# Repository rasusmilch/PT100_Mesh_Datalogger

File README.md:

# PT100 + MAX31865 Temperature Data Logger (ESP32-S3, ESP-IDF)

This application turns an ESP32-S3 N8R2 into a UTC-centric PT100 data logger with FRAM-first buffering, SD-card CSV batching/verification, DS3231 RTC support, mesh streaming, and serial-console calibration.

## Hardware / wiring

All signal pins are configurable under `idf.py menuconfig -> PT100 Logger`:

- Shared SPI bus: `MOSI`, `MISO`, `SCLK`
- Chip-selects: `MAX31865 CS`, `FRAM CS`, `SD CS`
- DS3231 I2C: `SDA`, `SCL` (address selectable)

Configure mesh root/leaf role and Wi-Fi credentials in the same menu.

## Build / flash

```bash
idf.py set-target esp32s3
idf.py menuconfig   # configure pins, mesh role, batch sizes, flush thresholds
idf.py build flash monitor
```

## Logging pipeline (FRAM → SD with verification)

- Sensor task samples MAX31865 at `log interval` (NVS-backed).
- Each record is appended as a fixed-size binary struct (with CRC) to a FRAM ring buffer; the persistent header tracks read/write indices and the next sequence number.
- The SD task builds large CSV batches (~64–256 KB, configurable) from FRAM without consuming it, then:
  1. Appends the batch to the daily CSV file (`YYYY-MM-DD.csv`) with `setvbuf` buffering.
  2. `fflush()` + `fsync()`.
  3. Reads back the appended region and checks SHA-256.
  4. On mismatch: truncates to the original size and leaves FRAM untouched.
  5. On success: consumes the matching FRAM records.
- CSV header (written once per day):  
  `schema_ver,record_id,seq,epoch_utc,iso8601_local,raw_rtd_ohms,raw_temp_c,cal_temp_c,flags,node_id`
- FRAM is limited (default 32 KB); when it fills, logging pauses (no overwrite) until a flush frees space. A `fram_full` flag surfaces via `status`.

### Resume / crash safety

- On boot or day rollover the logger:
  1. Opens today’s file, truncates to the last newline if the tail was partial.
  2. Scans the tail to find the last written `seq`.
  3. Drops any FRAM records with `seq <= last_sd_seq` to guarantee no duplicates.
- If FRAM corruption is detected, consumption stops and the corrupted record can be skipped explicitly (see logs).

### Timekeeping

- DS3231 is treated as UTC and seeds system time at boot.
- Mesh root uses SNTP, updates DS3231, and broadcasts time over the mesh; leaves can request/broadcast time updates.

## Serial console commands

- `status`
- `raw` (one sample: raw/calibrated temp + resistance)
- `log interval <ms>`
- `log watermark <records>` (FRAM flush high-water mark)
- `log flush_period <ms>` (periodic SD flush interval)
- `log batch <bytes>` (target SD batch size)
- `log show`
- `cal clear`
- `cal add <raw_c> <actual_c>`
- `cal list`
- `cal apply` (1 point = offset-only; 2–4 points fit deg1–deg3)
- `flush` (best-effort FRAM→SD flush with verification)
- `diag check` (diagnostics mode only; sensor/FRAM/SD/mesh/time quick health check)

All configuration changes persist to NVS.

## Mesh / host streaming

### Mesh mode (leaf → root → broker/serial)

- Leaf nodes publish samples into the mesh; logging to FRAM continues if the
  mesh or upstream network is down.
- The root bridges mesh records to the MQTT broker and/or the DATA UART (CSV),
  and these exports are best-effort only.

### Direct Wi-Fi leaf mode (leaf → broker)

- Leaves can bypass the mesh and publish directly to the broker when configured
  for direct Wi-Fi.

FRAM/SD logging plus the DATA UART output never depend on network availability.

- Leaf nodes send samples upstream; logging to FRAM continues if mesh is down.
- Root node prints one CSV row per record over UART (after the CSV header).

Root upstream router credentials can be provided via the `wifi_ssid` /
`wifi_pass` NVS settings (from your console tooling or provisioning flow). If
those are not set, the root falls back to
`CONFIG_APP_WIFI_ROUTER_SSID` / `CONFIG_APP_WIFI_ROUTER_PASSWORD` in Kconfig.

## Test plan

1. **Calibration persistence**: Add points, apply, reboot, and confirm `status` shows the same coefficients and calibrated readings remain adjusted.
2. **Batching size**: Monitor SD writes (logic analyzer or debug prints) to confirm large buffered writes (64–256 KB) rather than per-sample writes.
3. **Crash during flush**: Pull power mid-flush; on reboot confirm the CSV tail is repaired and no duplicated `seq` appears on SD after FRAM drains.
4. **Tail repair**: Manually append a partial line to a CSV, reboot, and confirm it is truncated to the last newline automatically.
5. **Mesh resilience**: Run leaves with the root powered off; verify local FRAM accumulation and later FRAM→SD flush when root/SD returns.
6. **SD removal**: Unmount/remove SD, ensure FRAM continues to grow; remount and verify backlogged records flush with verified appends.

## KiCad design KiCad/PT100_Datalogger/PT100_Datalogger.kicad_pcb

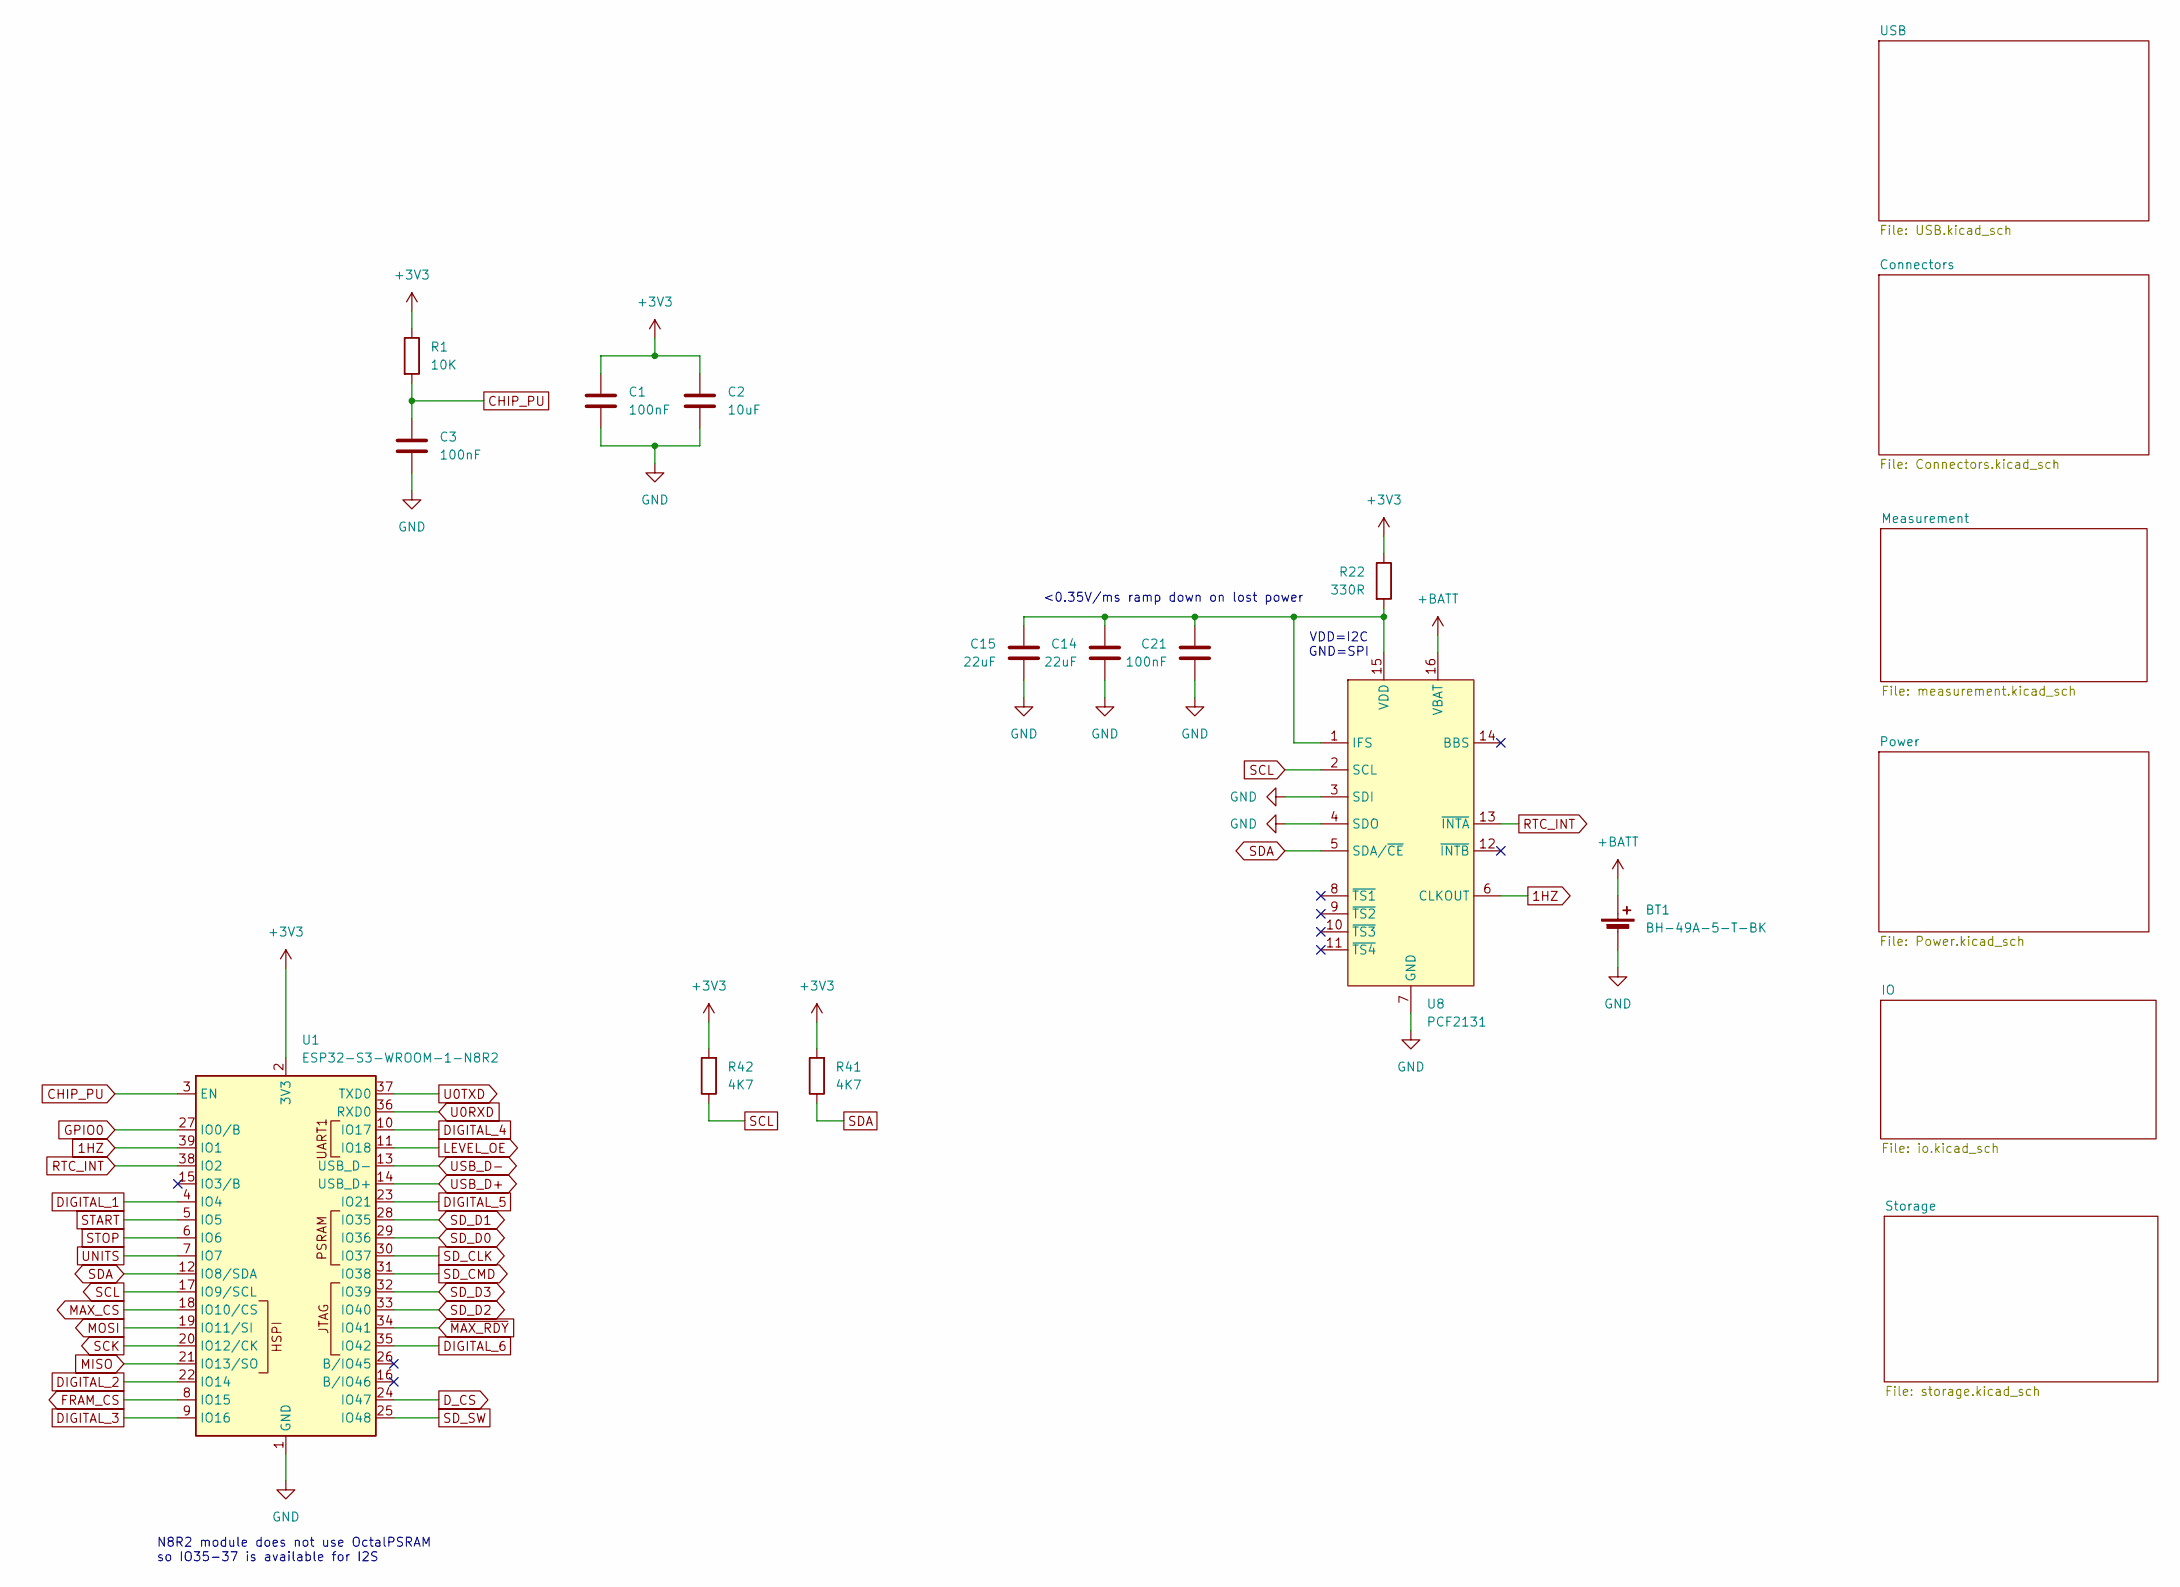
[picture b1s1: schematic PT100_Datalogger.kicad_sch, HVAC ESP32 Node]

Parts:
BT1: BH-49A-5-T-BK; BH-49A-5-T-BK_ADM
C1, C3, C21: 100nF; C_0603_1608Metric_Pad1.08x0.95mm_HandSolder
C2: 10uF; C_0805_2012Metric_Pad1.18x1.45mm_HandSolder
C14, C15: 22uF; C_0805_2012Metric_Pad1.18x1.45mm_HandSolder
R1: 10K; R_0603_1608Metric_Pad0.98x0.95mm_HandSolder
R22: 330R; R_0603_1608Metric_Pad0.98x0.95mm_HandSolder
R41, R42: 4K7; R_0603_1608Metric_Pad0.98x0.95mm_HandSolder
U1: ESP32-S3-WROOM-1-N8R2; ESP32-S3-WROOM-1
U8: PCF2131; 16-HLSON

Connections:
1HZ: U1.39 (IO1), U8.6 (CLKOUT)
+3V3: C1.1, C2.1, R1.1, R22.1, R41.2, R42.2, U1.2 (3V3); also elsewhere on the board
+BATT: BT1.1 (+), U8.16 (VBAT)
CHIP_PU: C3.1, R1.2, U1.3 (EN); also elsewhere on the board
DIGITAL_1: U1.4 (IO4); also elsewhere on the board
DIGITAL_2: U1.22 (IO14); also elsewhere on the board
DIGITAL_3: U1.9 (IO16); also elsewhere on the board
DIGITAL_4: U1.10 (IO17); also elsewhere on the board
DIGITAL_5: U1.23 (IO21); also elsewhere on the board
DIGITAL_6: U1.35 (IO42); also elsewhere on the board
D_CS: U1.24 (IO47); also elsewhere on the board
FRAM_CS: U1.8 (IO15); also elsewhere on the board
GND: BT1.2 (-), C1.2, C2.2, C3.2, C14.2, C15.2, C21.2, U1.1 (GND), U1.40 (GND), U1.41 (GND), U8.3 (SDI), U8.4 (SDO), U8.7 (GND); also elsewhere on the board
GPIO0: U1.27 (IO0/B); also elsewhere on the board
LEVEL_OE: U1.11 (IO18); also elsewhere on the board
MAX_CS: U1.18 (IO10/CS); also elsewhere on the board
MISO: U1.21 (IO13/SO); also elsewhere on the board
MOSI: U1.19 (IO11/SI); also elsewhere on the board
unnamed: C14.1, C15.1, C21.1, R22.2, U8.1 (IFS), U8.15 (VDD)
RTC_INT: U1.38 (IO2), U8.13 (~INTA)
SCK: U1.20 (IO12/CK); also elsewhere on the board
SCL: R42.1, U1.17 (IO9/SCL), U8.2 (SCL); also elsewhere on the board
SDA: R41.1, U1.12 (IO8/SDA), U8.5 (SDA/~CE); also elsewhere on the board
SD_CLK: U1.30 (IO37); also elsewhere on the board
SD_CMD: U1.31 (IO38); also elsewhere on the board
SD_D0: U1.29 (IO36); also elsewhere on the board
SD_D1: U1.28 (IO35); also elsewhere on the board
SD_D2: U1.33 (IO40); also elsewhere on the board
SD_D3: U1.32 (IO39); also elsewhere on the board
SD_SW: U1.25 (IO48); also elsewhere on the board
START: U1.5 (IO5); also elsewhere on the board
STOP: U1.6 (IO6); also elsewhere on the board
U0RXD: U1.36 (RXD0); also elsewhere on the board
U0TXD: U1.37 (TXD0); also elsewhere on the board
UNITS: U1.7 (IO7); also elsewhere on the board
USB_D+: U1.14 (USB_D+); also elsewhere on the board
USB_D-: U1.13 (USB_D-); also elsewhere on the board
~MAX_RDY: U1.34 (IO41); also elsewhere on the board

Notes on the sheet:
<0.35V/ms ramp down on lost power
VDD=I2C GND=SPI
N8R2 module does not use OctalPSRAM so IO35-37 is available for I2S

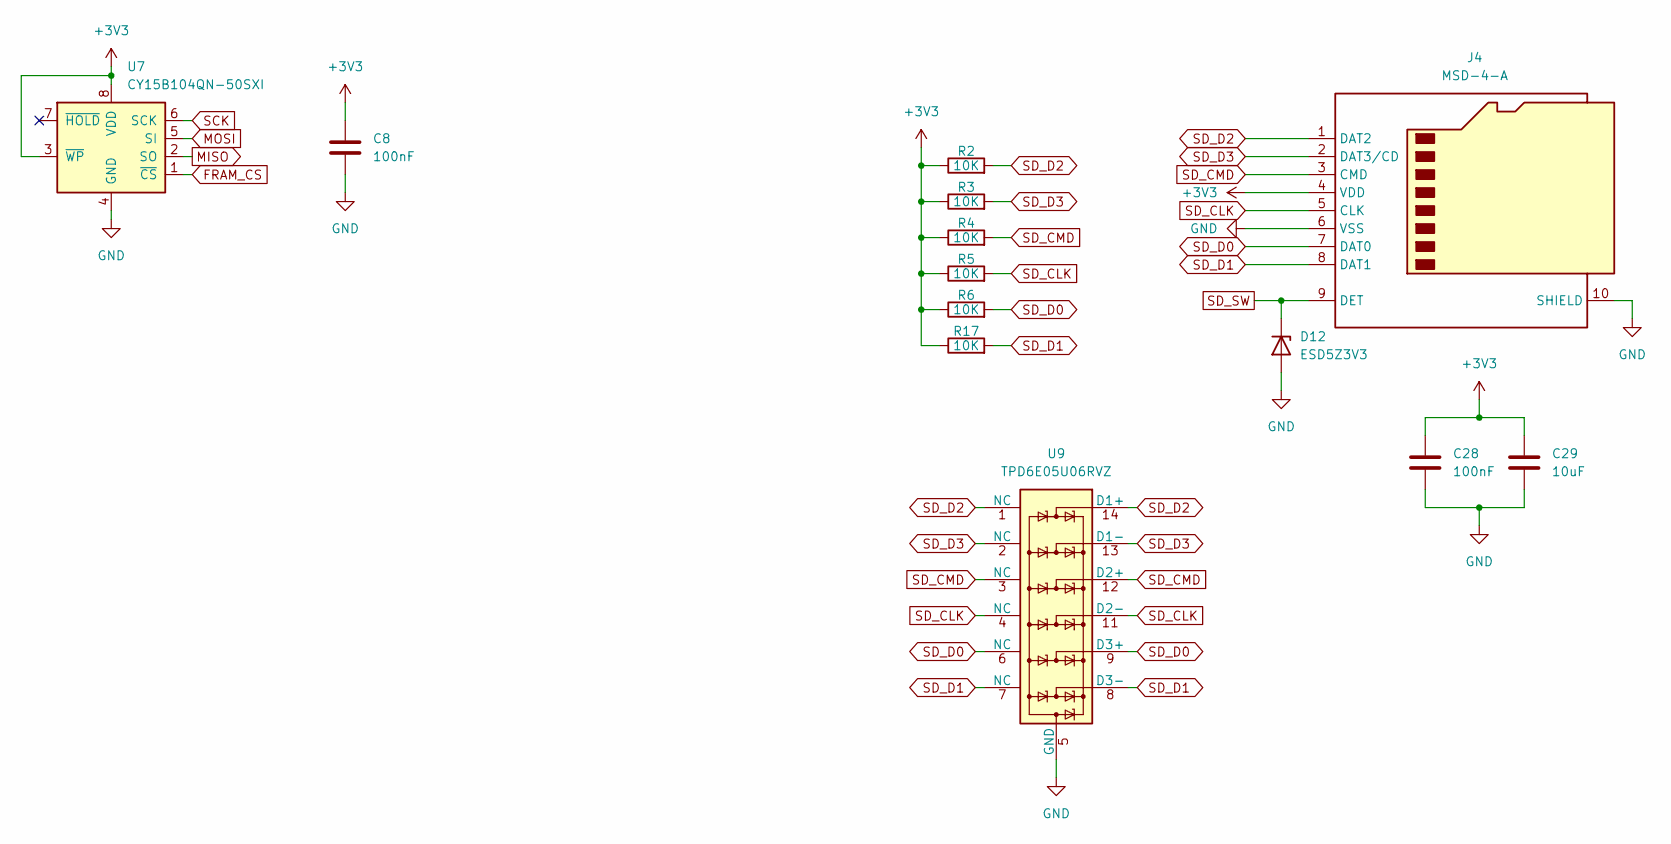
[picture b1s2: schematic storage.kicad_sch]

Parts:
C8, C28: 100nF; C_0603_1608Metric_Pad1.08x0.95mm_HandSolder
C29: 10uF; C_0805_2012Metric_Pad1.18x1.45mm_HandSolder
D12: ESD5Z3V3; D_SOD-523
J4: MSD-4-A; CUI_MSD-4-A
R2, R3, R4, R5, R6, R17: 10K; R_0603_1608Metric_Pad0.98x0.95mm_HandSolder
U7: CY15B104QN-50SXI; SOIC-8_5.3x5.3mm_P1.27mm
U9: TPD6E05U06RVZ; Texas_R-PUSON-N14

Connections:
+3V3: C8.1, C28.1, C29.1, J4.4 (VDD), R2.1, R3.1, R4.1, R5.1, R6.1, R17.1, U7.3 (~WP), U7.8 (VDD); also elsewhere on the board
FRAM_CS: U7.1 (~CS); also elsewhere on the board
GND: C8.2, C28.2, C29.2, D12.2 (A), J4.6 (VSS), J4.10 (SHIELD), U7.4 (GND), U9.5 (GND), U9.10 (GND); also elsewhere on the board
MISO: U7.2 (SO); also elsewhere on the board
MOSI: U7.5 (SI); also elsewhere on the board
SCK: U7.6 (SCK); also elsewhere on the board
SD_CLK: J4.5 (CLK), R5.2, U9.4 (NC), U9.11 (D2-); also elsewhere on the board
SD_CMD: J4.3 (CMD), R4.2, U9.3 (NC), U9.12 (D2+); also elsewhere on the board
SD_D0: J4.7 (DAT0), R6.2, U9.6 (NC), U9.9 (D3+); also elsewhere on the board
SD_D1: J4.8 (DAT1), R17.2, U9.7 (NC), U9.8 (D3-); also elsewhere on the board
SD_D2: J4.1 (DAT2), R2.2, U9.1 (NC), U9.14 (D1+); also elsewhere on the board
SD_D3: J4.2 (DAT3/CD), R3.2, U9.2 (NC), U9.13 (D1-); also elsewhere on the board
SD_SW: D12.1 (K), J4.9 (DET); also elsewhere on the board

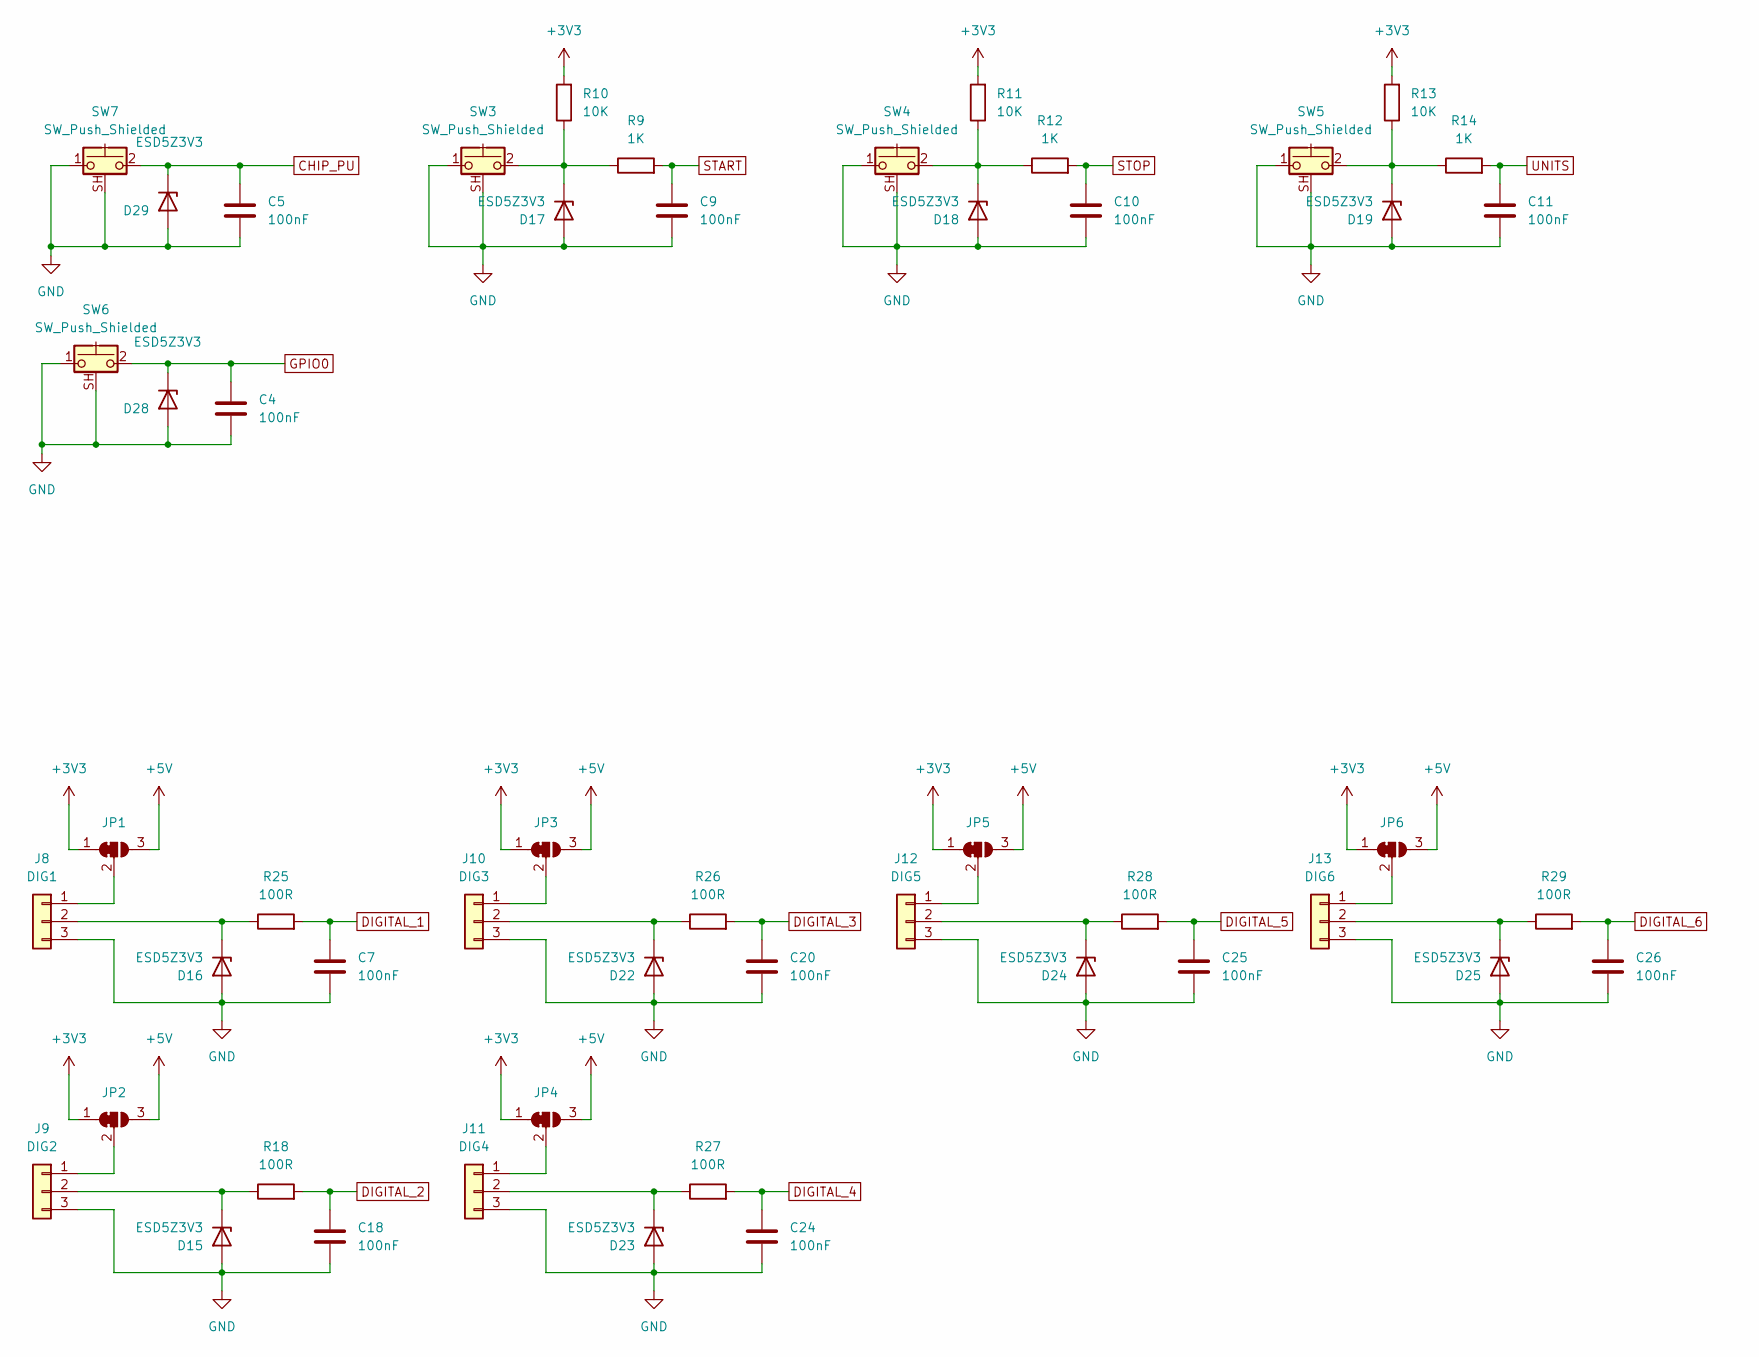
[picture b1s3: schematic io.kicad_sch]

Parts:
C4, C5, C7, C9, C10, C11, C18, C20, C24, C25, C26: 100nF; C_0603_1608Metric_Pad1.08x0.95mm_HandSolder
D15, D16, D17, D18, D19, D22, D23, D24, D25, D28, D29: ESD5Z3V3; D_SOD-523
J8: DIG1; Molex_KK-254_AE-6410-03A_1x03_P2.54mm_Vertical
J9: DIG2; Molex_KK-254_AE-6410-03A_1x03_P2.54mm_Vertical
J10: DIG3; Molex_KK-254_AE-6410-03A_1x03_P2.54mm_Vertical
J11: DIG4; Molex_KK-254_AE-6410-03A_1x03_P2.54mm_Vertical
J12: DIG5; Molex_KK-254_AE-6410-03A_1x03_P2.54mm_Vertical
J13: DIG6; Molex_KK-254_AE-6410-03A_1x03_P2.54mm_Vertical
JP1, JP2, JP3, JP4, JP5, JP6: SolderJumper_3_Bridged12; SolderJumper-3_P1.3mm_Bridged12_RoundedPad1.0x1.5mm
R9, R12, R14: 1K; R_0603_1608Metric_Pad0.98x0.95mm_HandSolder
R10, R11, R13: 10K; R_0603_1608Metric_Pad0.98x0.95mm_HandSolder
R18, R25, R26, R27, R28, R29: 100R; R_0603_1608Metric_Pad0.98x0.95mm_HandSolder
SW3, SW4, SW5, SW6, SW7: SW_Push_Shielded; SW_SPST_B3U-1100P

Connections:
+3V3: JP1.1 (A), JP2.1 (A), JP3.1 (A), JP4.1 (A), JP5.1 (A), JP6.1 (A), R10.2, R11.2, R13.2; also elsewhere on the board
+5V: JP1.3 (B), JP2.3 (B), JP3.3 (B), JP4.3 (B), JP5.3 (B), JP6.3 (B); also elsewhere on the board
CHIP_PU: C5.1, D29.1 (K), SW7.2; also elsewhere on the board
DIGITAL_1: C7.1, R25.2; also elsewhere on the board
DIGITAL_2: C18.1, R18.2; also elsewhere on the board
DIGITAL_3: C20.1, R26.2; also elsewhere on the board
DIGITAL_4: C24.1, R27.2; also elsewhere on the board
DIGITAL_5: C25.1, R28.2; also elsewhere on the board
DIGITAL_6: C26.1, R29.2; also elsewhere on the board
GND: C4.2, C5.2, C7.2, C9.2, C10.2, C11.2, C18.2, C20.2, C24.2, C25.2, C26.2, D15.2 (A), D16.2 (A), D17.2 (A), D18.2 (A), D19.2 (A), D22.2 (A), D23.2 (A), D24.2 (A), D25.2 (A), D28.2 (A), D29.2 (A), J8.3, J9.3, J10.3, J11.3, J12.3, J13.3, SW3.1, SW3.SH (B), SW4.1, SW4.SH (B), SW5.1, SW5.SH (B), SW6.1, SW6.SH (B), SW7.1, SW7.SH (B); also elsewhere on the board
GPIO0: C4.1, D28.1 (K), SW6.2; also elsewhere on the board
unnamed: D15.1 (K), J9.2, R18.1
unnamed: D16.1 (K), J8.2, R25.1
unnamed: D17.1 (K), R9.1, R10.1, SW3.2
unnamed: D18.1 (K), R11.1, R12.1, SW4.2
unnamed: D19.1 (K), R13.1, R14.1, SW5.2
unnamed: D22.1 (K), J10.2, R26.1
unnamed: D23.1 (K), J11.2, R27.1
unnamed: D24.1 (K), J12.2, R28.1
unnamed: D25.1 (K), J13.2, R29.1
unnamed: J8.1, JP1.2 (C)
unnamed: J9.1, JP2.2 (C)
unnamed: J10.1, JP3.2 (C)
unnamed: J11.1, JP4.2 (C)
unnamed: J12.1, JP5.2 (C)
unnamed: J13.1, JP6.2 (C)
START: C9.1, R9.2; also elsewhere on the board
STOP: C10.1, R12.2; also elsewhere on the board
UNITS: C11.1, R14.2; also elsewhere on the board

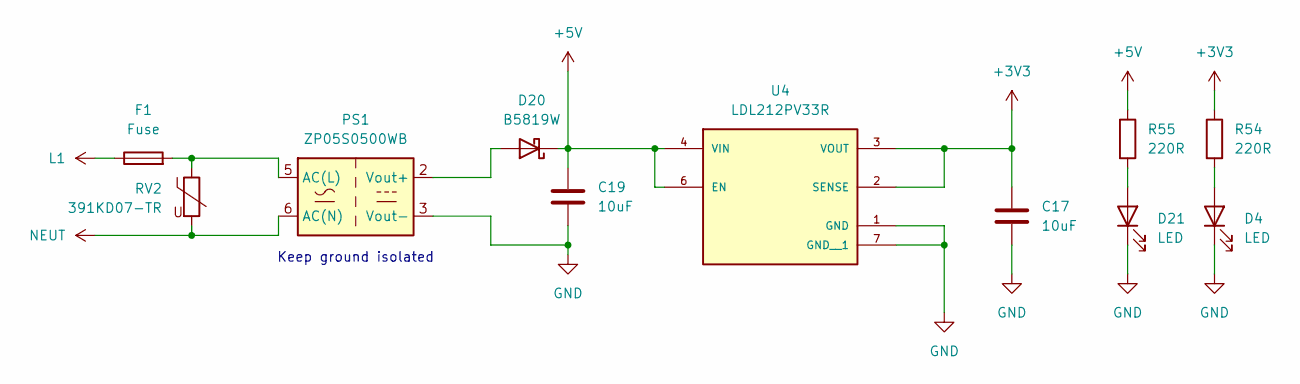
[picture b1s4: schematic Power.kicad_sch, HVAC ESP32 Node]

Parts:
C17, C19: 10uF; C_0805_2012Metric_Pad1.18x1.45mm_HandSolder
D4, D21: LED; LED_0603_1608Metric_Pad1.05x0.95mm_HandSolder
D20: B5819W; D_SOD-123
F1: Fuse; Fuseholder_Clip-5x20mm_Littelfuse_111_Lateral_P18.80x5.00mm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
PS1: ZP05S0500WB
R54, R55: 220R; R_0603_1608Metric_Pad0.98x0.95mm_HandSolder
RV2: 391KD07-TR; RV_Disc_D7mm_W5.4mm_P5mm
U4: LDL212PV33R; SON50P200X200X80-7N; PARTREV 5

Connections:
+3V3: C17.1, R54.1, U4.2 (SENSE), U4.3 (VOUT); also elsewhere on the board
+5V: C19.1, D20.1 (K), R55.1, U4.4 (VIN), U4.6 (EN); also elsewhere on the board
GND: C17.2, C19.2, D4.1 (K), D21.1 (K), PS1.3 (Vout-), U4.1 (GND), U4.7 (GND__1); also elsewhere on the board
L1: F1.1; also elsewhere on the board
NEUT: PS1.6 (AC(N)), RV2.2; also elsewhere on the board
unnamed: D4.2 (A), R54.2
unnamed: D20.2 (A), PS1.2 (Vout+)
unnamed: D21.2 (A), R55.2
unnamed: F1.2, PS1.5 (AC(L)), RV2.1

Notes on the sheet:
Keep ground isolated

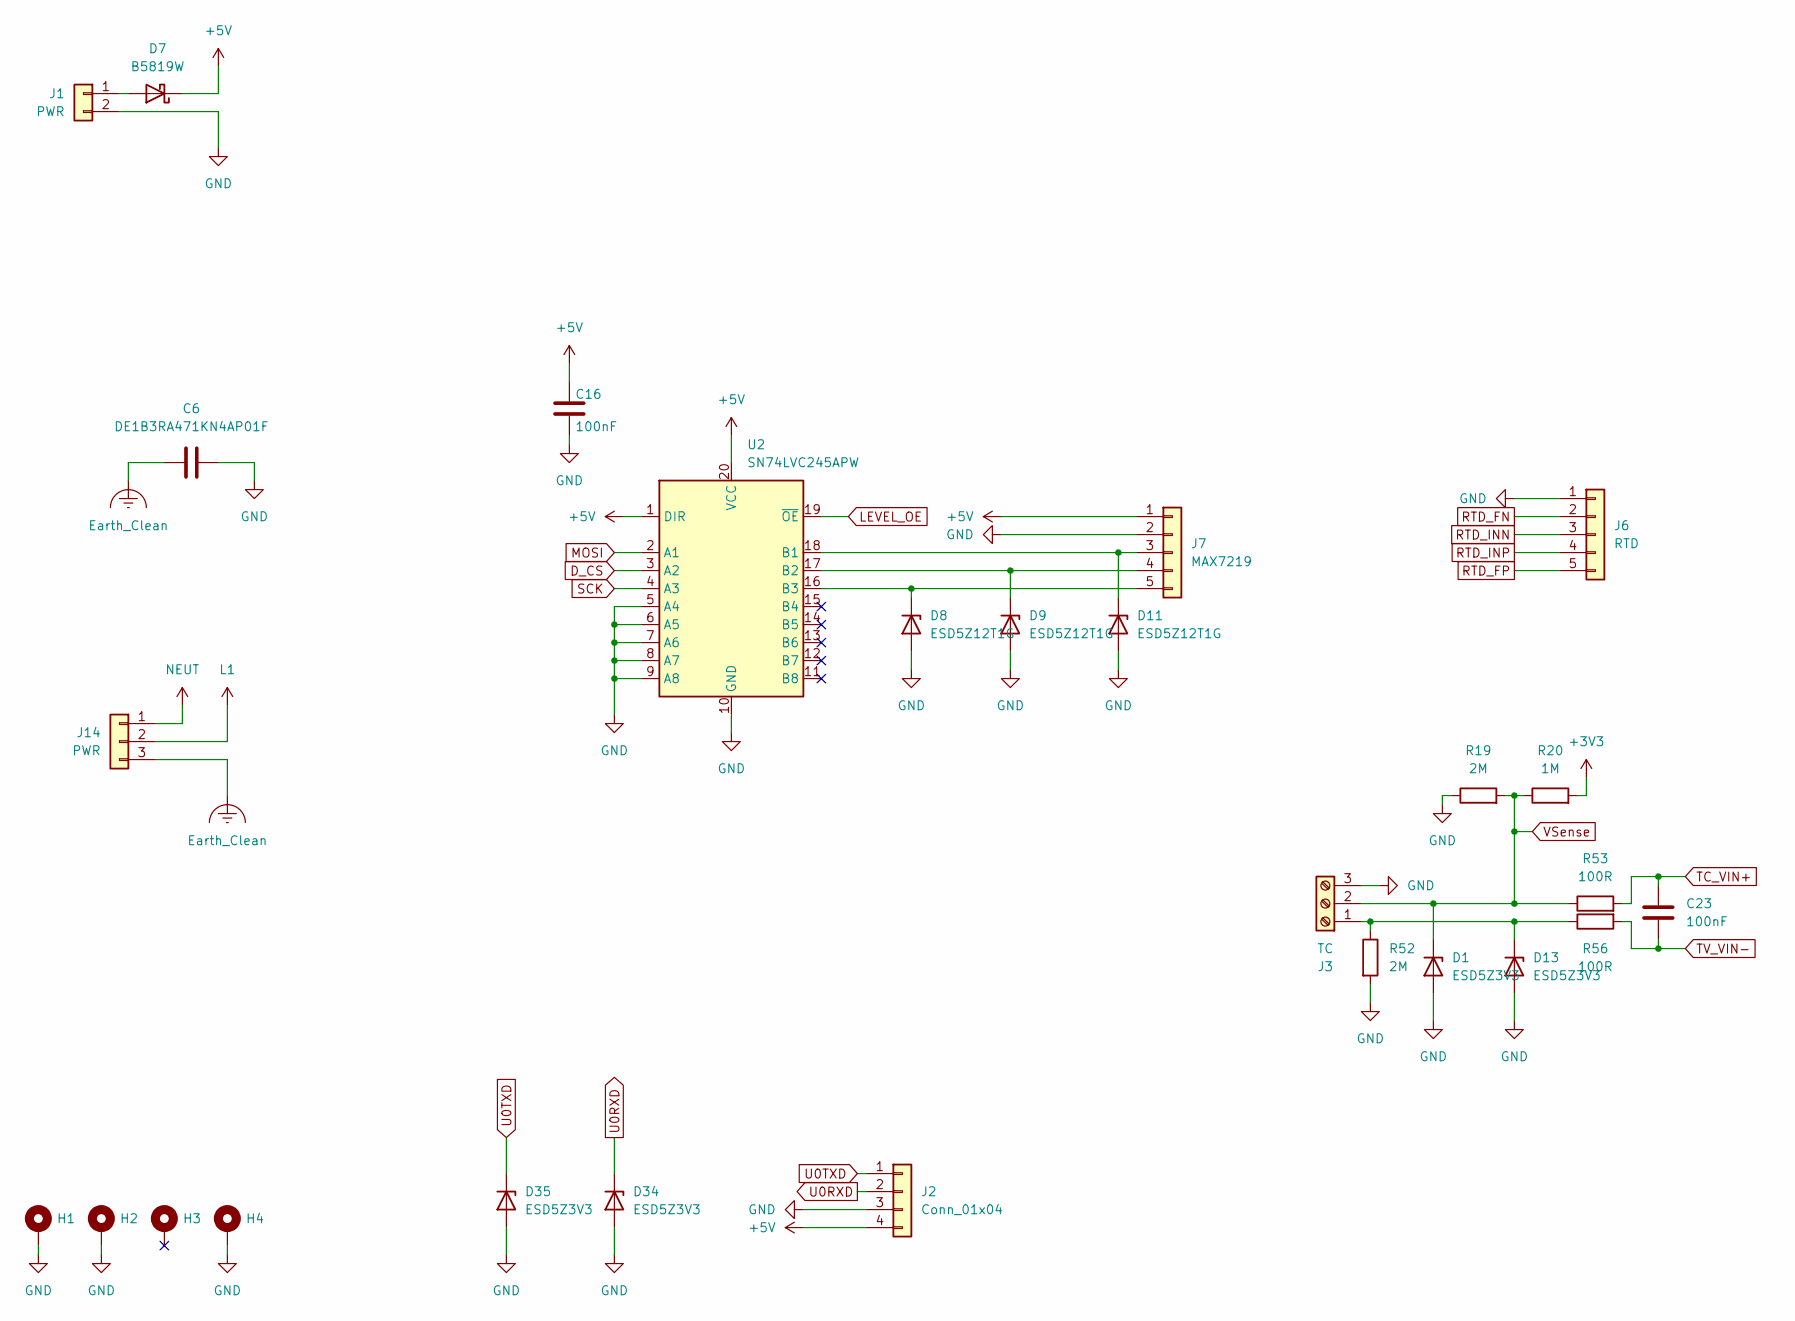
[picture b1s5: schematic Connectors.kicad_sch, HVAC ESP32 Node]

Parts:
C6: DE1B3RA471KN4AP01F; C_Disc_D7.5mm_W5.0mm_P10.00mm
C16, C23: 100nF; C_0603_1608Metric_Pad1.08x0.95mm_HandSolder
D1, D13, D34, D35: ESD5Z3V3; D_SOD-523
D7: B5819W; D_SOD-123
D8, D9, D11: ESD5Z12T1G; D_SOD-523
H1, H2, H3, H4: MountingHole_Pad; MountingHole_3.2mm_M3_Pad
J1: PWR; Molex_KK-254_AE-6410-02A_1x02_P2.54mm_Vertical
J2: Conn_01x04; Molex_KK-254_AE-6410-04A_1x04_P2.54mm_Vertical
J3: TC; TerminalBlock_Onshore-3_P2.54mm
J6: RTD; Molex_KK-254_AE-6410-05A_1x05_P2.54mm_Vertical
J7: MAX7219; Molex_KK-254_AE-6410-05A_1x05_P2.54mm_Vertical
J14: PWR; JST_VH_B3P-VH_1x03_P3.96mm_Vertical
R19, R52: 2M; R_0603_1608Metric_Pad0.98x0.95mm_HandSolder
R20: 1M; R_0603_1608Metric_Pad0.98x0.95mm_HandSolder
R53, R56: 100R; R_0603_1608Metric_Pad0.98x0.95mm_HandSolder
U2: SN74LVC245APW; TSSOP-20_4.4x6.5mm_P0.65mm

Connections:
+3V3: R20.2; also elsewhere on the board
+5V: C16.1, D7.1 (K), J2.4, J7.1, U2.1 (DIR), U2.20 (VCC); also elsewhere on the board
D_CS: U2.3 (A2); also elsewhere on the board
Earth_Clean: C6.1, J14.3
GND: C6.2, C16.2, D1.2 (A), D8.2 (A), D9.2 (A), D11.2 (A), D13.2 (A), D34.2 (A), D35.2 (A), H1.1, H2.1, H4.1, J1.2, J2.3, J3.3, J6.1, J7.2, R19.1, R52.2, U2.5 (A4), U2.6 (A5), U2.7 (A6), U2.8 (A7), U2.9 (A8), U2.10 (GND); also elsewhere on the board
L1: J14.2; also elsewhere on the board
LEVEL_OE: U2.19 (~OE); also elsewhere on the board
MOSI: U2.2 (A1); also elsewhere on the board
NEUT: J14.1; also elsewhere on the board
unnamed: D7.2 (A), J1.1
unnamed: D8.1 (K), J7.5, U2.16 (B3)
unnamed: D9.1 (K), J7.4, U2.17 (B2)
unnamed: D11.1 (K), J7.3, U2.18 (B1)
unnamed: D13.1 (K), J3.1, R52.1, R56.1
RTD_FN: J6.2; also elsewhere on the board
RTD_FP: J6.5; also elsewhere on the board
RTD_INN: J6.3; also elsewhere on the board
RTD_INP: J6.4; also elsewhere on the board
SCK: U2.4 (A3); also elsewhere on the board
TC_VIN+: C23.1, R53.2; also elsewhere on the board
TV_VIN-: C23.2, R56.2; also elsewhere on the board
U0RXD: D34.1 (K), J2.2; also elsewhere on the board
U0TXD: D35.1 (K), J2.1; also elsewhere on the board
VSense: D1.1 (K), J3.2, R19.2, R20.1, R53.1; also elsewhere on the board

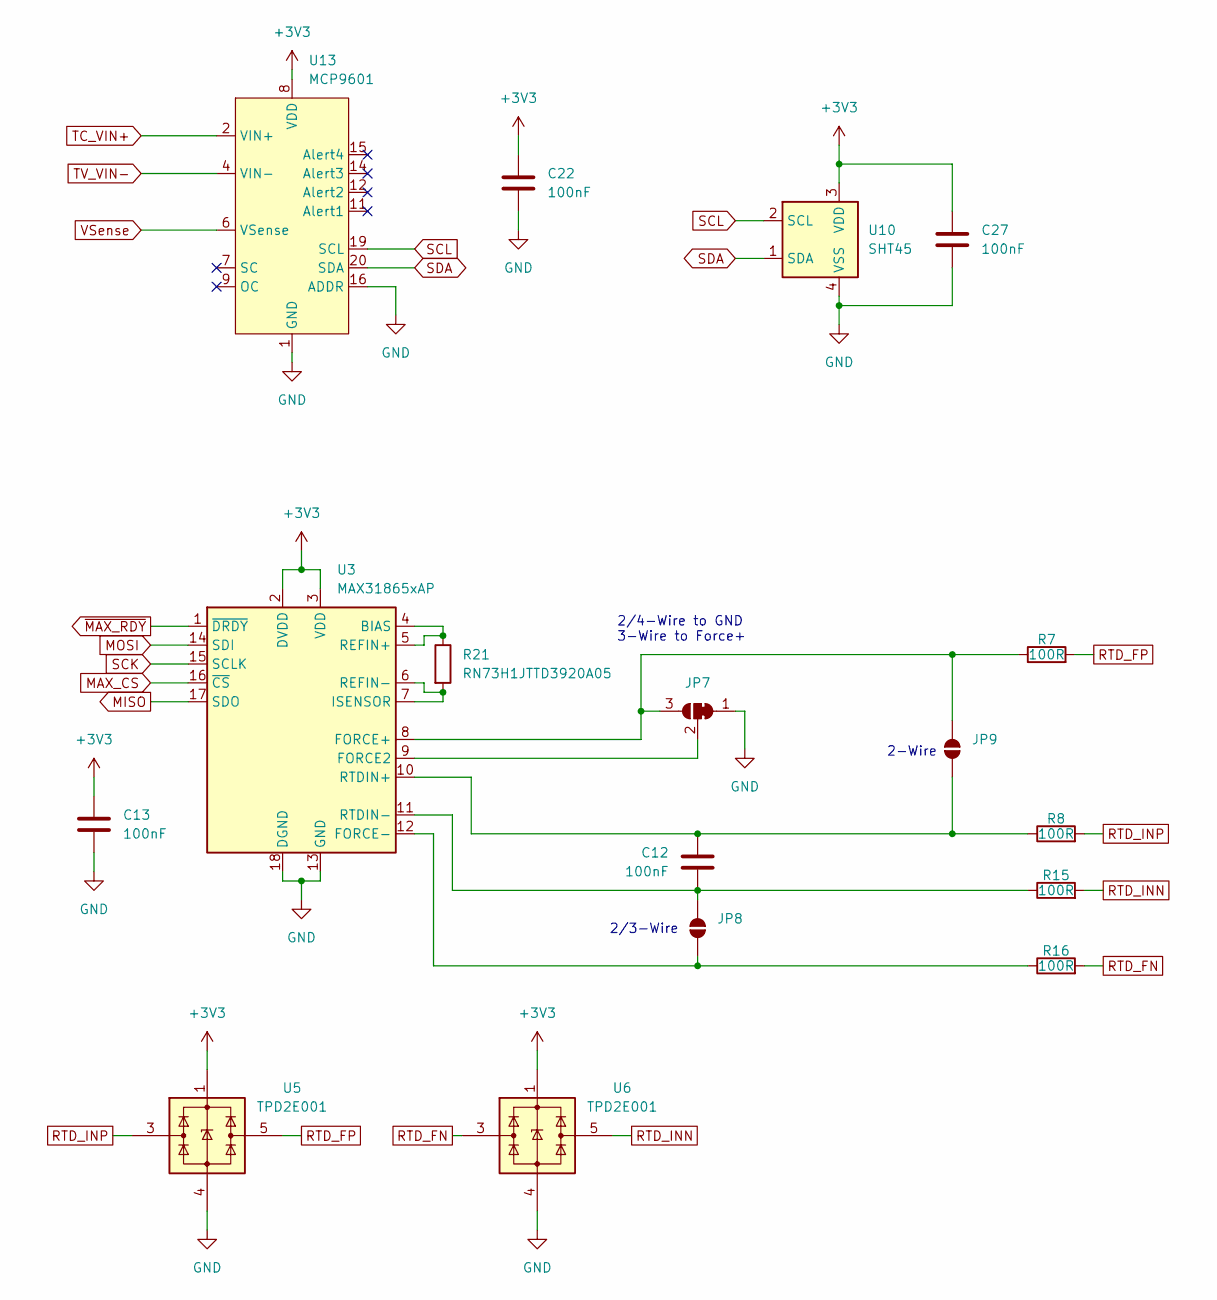
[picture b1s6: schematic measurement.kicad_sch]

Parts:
C12, C13, C22, C27: 100nF; C_0603_1608Metric_Pad1.08x0.95mm_HandSolder
JP7: SolderJumper_3_Bridged12; SolderJumper-3_P1.3mm_Bridged12_Pad1.0x1.5mm
JP8, JP9: SolderJumper_2_Open; SolderJumper-2_P1.3mm_Open_TrianglePad1.0x1.5mm
R7, R8, R15, R16: 100R; R_0603_1608Metric_Pad0.98x0.95mm_HandSolder
R21: RN73H1JTTD3920A05; R_0603_1608Metric_Pad0.98x0.95mm_HandSolder
U3: MAX31865xAP; SSOP-20_5.3x7.2mm_P0.65mm
U5, U6: TPD2E001; SOT-553
U10: SHT45; Sensirion_DFN-4_1.5x1.5mm_P0.8mm_SHT4x_NoCentralPad
U13: MCP9601; Texas_RGW0020A_VQFN-20-1EP_5x5mm_P0.65mm_EP3.15x3.15mm_Ther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

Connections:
+3V3: C13.1, C22.1, C27.1, U3.2 (DVDD), U3.3 (VDD), U5.1, U6.1, U10.3 (VDD), U13.8 (VDD); also elsewhere on the board
GND: C13.2, C22.2, C27.2, JP7.1 (A), U3.13 (GND), U3.18 (DGND), U3.19 (GND), U5.4, U6.4, U10.4 (VSS), U13.1 (GND), U13.3 (GND), U13.5 (GND), U13.10 (GND), U13.13 (GND), U13.16 (ADDR), U13.17 (GND), U13.18 (GND), U13.21 (EP); also elsewhere on the board
MAX_CS: U3.16 (~CS); also elsewhere on the board
MISO: U3.17 (SDO); also elsewhere on the board
MOSI: U3.14 (SDI); also elsewhere on the board
unnamed: JP7.3 (B), JP9.2 (B), R7.1, U3.8 (FORCE+)
unnamed: JP7.2 (C), U3.9 (FORCE2)
unnamed: JP8.1 (A), R16.1, U3.12 (FORCE-)
unnamed: C12.2, JP8.2 (B), R15.1, U3.11 (RTDIN-)
unnamed: C12.1, JP9.1 (A), R8.1, U3.10 (RTDIN+)
unnamed: R21.1, U3.4 (BIAS), U3.5 (REFIN+)
unnamed: R21.2, U3.6 (REFIN-), U3.7 (ISENSOR)
RTD_FN: R16.2, U6.3; also elsewhere on the board
RTD_FP: R7.2, U5.5; also elsewhere on the board
RTD_INN: R15.2, U6.5; also elsewhere on the board
RTD_INP: R8.2, U5.3; also elsewhere on the board
SCK: U3.15 (SCLK); also elsewhere on the board
SCL: U10.2 (SCL), U13.19 (SCL); also elsewhere on the board
SDA: U10.1 (SDA), U13.20 (SDA); also elsewhere on the board
TC_VIN+: U13.2 (VIN+); also elsewhere on the board
TV_VIN-: U13.4 (VIN-); also elsewhere on the board
VSense: U13.6 (VSense); also elsewhere on the board
~MAX_RDY: U3.1 (~DRDY); also elsewhere on the board

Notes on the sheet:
2/3-Wire
2/4-Wire to GND 3-Wire to Force+
2-Wire

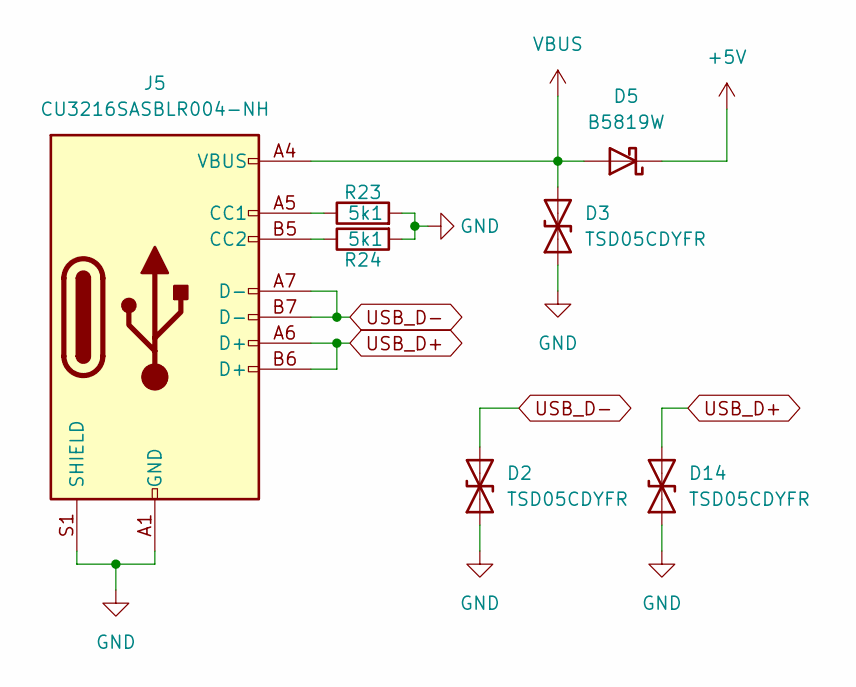
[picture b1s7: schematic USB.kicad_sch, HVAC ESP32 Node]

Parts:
D2, D3, D14: TSD05CDYFR; D_SOD-323_HandSoldering
D5: B5819W; D_SOD-123
J5: CU3216SASBLR004-NH; CONN_CU3216SASBLR004-NH_CVI
R23, R24: 5k1; R_0603_1608Metric_Pad0.98x0.95mm_HandSolder

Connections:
+5V: D5.1 (K); also elsewhere on the board
GND: D2.1 (A1), D3.1 (A1), D14.1 (A1), J5.A1 (GND), J5.A12 (GND), J5.B1 (GND), J5.B12 (GND), J5.S1 (SHIELD), R23.2, R24.2; also elsewhere on the board
unnamed: J5.A5 (CC1), R23.1
unnamed: J5.B5 (CC2), R24.1
USB_D+: D14.2 (A2), J5.A6 (D+), J5.B6 (D+); also elsewhere on the board
USB_D-: D2.2 (A2), J5.A7 (D-), J5.B7 (D-); also elsewhere on the board
VBUS: D3.2 (A2), D5.2 (A), J5.A4 (VBUS), J5.A9 (VBUS), J5.B4 (VBUS), J5.B9 (VBUS)

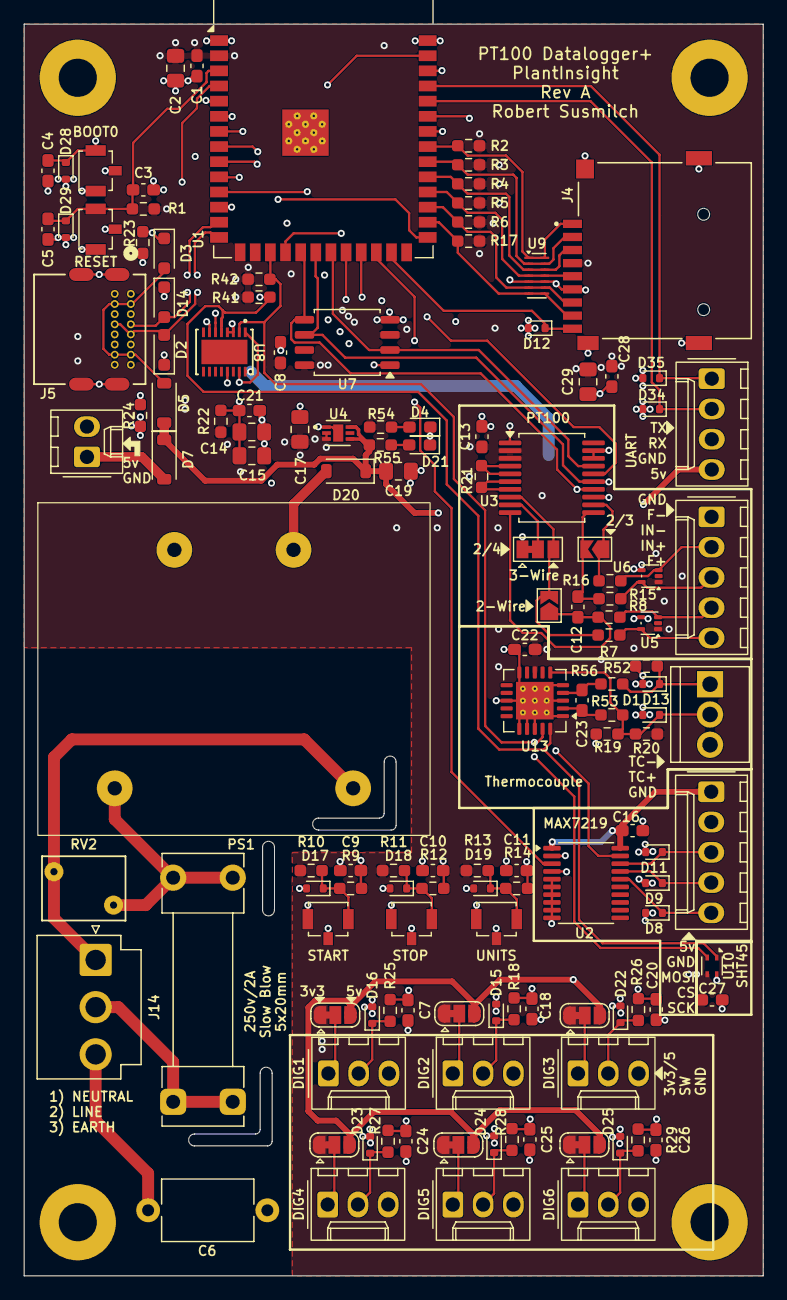
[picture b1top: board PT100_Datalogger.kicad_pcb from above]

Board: 4 copper layers, 62.0 x 105.0 mm, 139 parts (1 on the bottom side), 83 nets.
